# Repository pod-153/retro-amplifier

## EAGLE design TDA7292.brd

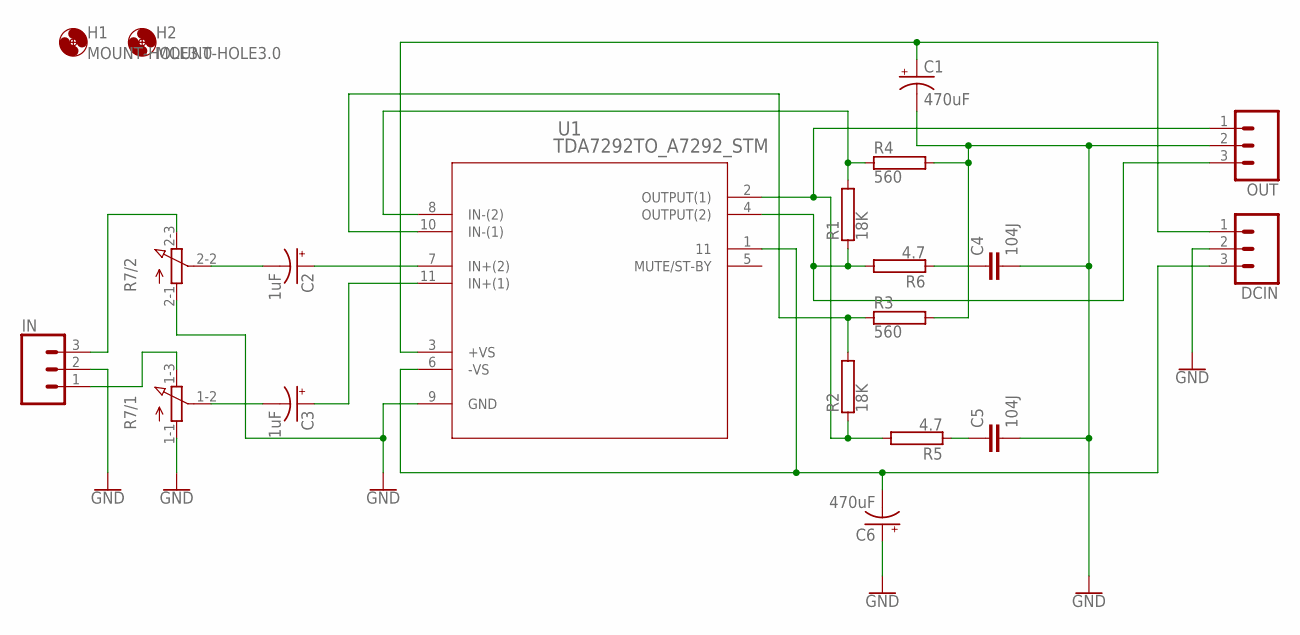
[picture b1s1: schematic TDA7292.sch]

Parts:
C1, C6: 470uF; CPOL-RADIAL-5MM-10MM
C2, C3: 1uF; CPOL-RADIAL-5MM-10MM
C4, C5: 104J; CAP-PTH-10MM
DCIN: CONN_03POLAR; MOLEX-1X3
H1, H2: MOUNT-HOLE3.0; 3,0
IN: CONN_03POLAR; MOLEX-1X3
OUT: CONN_03POLAR; MOLEX-1X3
R1, R2: 18K; RS1/2
R3, R4: 560; RS1/2
R5, R6: 4.7; RS1/2
R7: 3RP/1610G
U1: TDA7292TO_A7292_STM; TO_A7292_STM

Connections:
GND: C1.-, C4.2, C5.2, C6.+, DCIN.2, IN.2, OUT.2, R3.2, R4.2, R7.1-1 (A), R7.2-1 (A), U1.9 (GND)
unnamed: C6.-, DCIN.3, U1.1 (11), U1.6 (-VS)
unnamed: IN.1, R7.1-3 (E)
unnamed: IN.3, R7.2-3 (E)
unnamed: C3.-, R7.1-2 (S)
unnamed: C2.-, R7.2-2 (S)
unnamed: C2.+, U1.7 (IN+(2))
unnamed: C3.+, U1.11 (IN+(1))
unnamed: OUT.3, R1.1, R6.2, U1.4 (OUTPUT(2))
unnamed: R1.2, R4.1, U1.8 (IN-(2))
unnamed: C4.1, R6.1
unnamed: OUT.1, R2.1, R5.2, U1.2 (OUTPUT(1))
unnamed: C5.1, R5.1
unnamed: R2.2, R3.1, U1.10 (IN-(1))
VTOP: C1.+, DCIN.1, U1.3 (+VS)

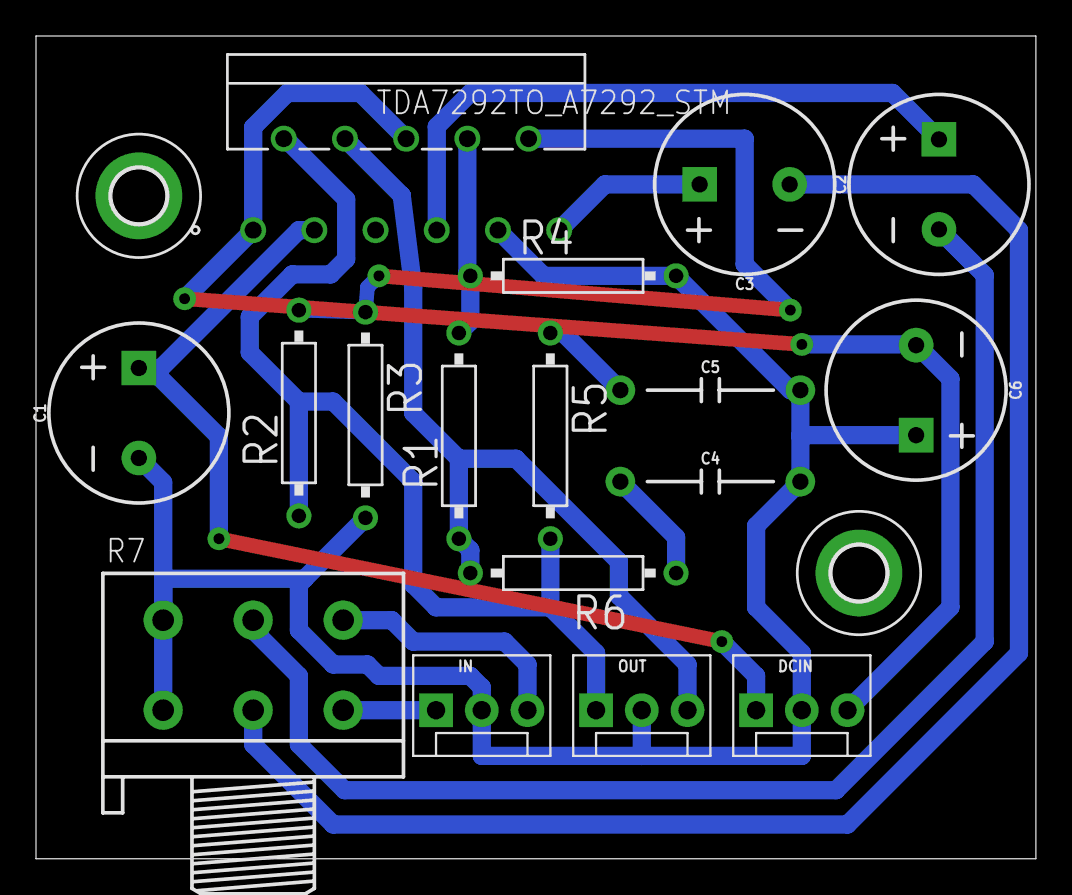
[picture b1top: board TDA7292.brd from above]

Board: 2 copper layers, 55.5 x 45.7 mm, 19 parts (0 on the bottom side), 15 nets.

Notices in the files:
parts and their libraries:
SparkFun-Capacitors: Licensing: Creative Commons ShareAlike 4.0 International - https://creativecommons.org/licenses/by-sa/4.0
COPYRIGHT: Copyright (C) 2022 Ultra Librarian. All rights reserved.
